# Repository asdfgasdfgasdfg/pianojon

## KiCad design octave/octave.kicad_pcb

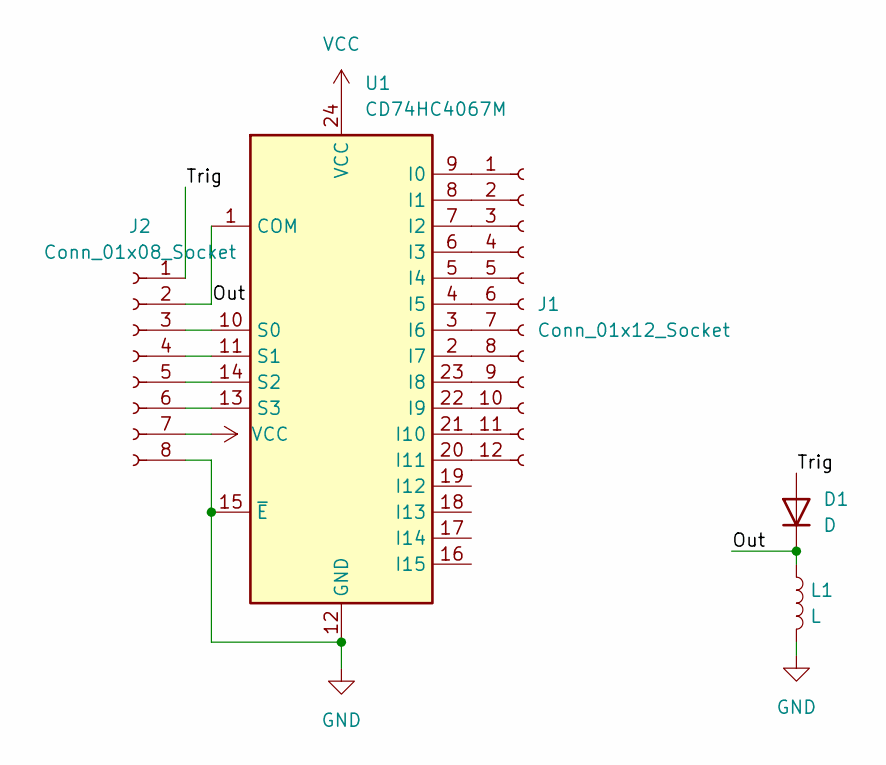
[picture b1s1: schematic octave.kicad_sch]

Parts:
D1: D; R_Axial_DIN0204_L3.6mm_D1.6mm_P2.54mm_Vertical
J1: Conn_01x12_Socket; PinHeader_1x12_P2.54mm_Vertical
J2: Conn_01x08_Socket; PinHeader_1x08_P2.54mm_Vertical
L1: L; L_Axial_L5.3mm_D2.2mm_P2.54mm_Vertical_Vishay_IM-1
U1: CD74HC4067M; DHVQFN-24_3.5x5.5mm_P0.5mm

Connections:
/Out: D1.1 (K), J2.2, L1.1, U1.1 (COM)
/Trig: D1.2 (A), J2.1
GND: J2.8, L1.2, U1.12 (GND), U1.15 (~E)
unnamed: J1.1, U1.9 (I0)
unnamed: J1.2, U1.8 (I1)
unnamed: J1.3, U1.7 (I2)
unnamed: J1.4, U1.6 (I3)
unnamed: J1.5, U1.5 (I4)
unnamed: J1.6, U1.4 (I5)
unnamed: J1.7, U1.3 (I6)
unnamed: J1.8, U1.2 (I7)
unnamed: J1.9, U1.23 (I8)
unnamed: J1.10, U1.22 (I9)
unnamed: J1.11, U1.21 (I10)
unnamed: J1.12, U1.20 (I11)
unnamed: J2.3, U1.10 (S0)
unnamed: J2.4, U1.11 (S1)
unnamed: J2.5, U1.14 (S2)
unnamed: J2.6, U1.13 (S3)
VCC: J2.7, U1.24 (VCC)

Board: 2 copper layers, 5 parts (0 on the bottom side), 20 nets, no tracks yet.

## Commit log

2025-09-12 init
2025-09-12 boilerplate
2025-09-12 Add initial content to README.md
2025-09-13 Added arduino files
2025-09-13 trying buf2 = 11
2025-09-15 pianojon audio works
